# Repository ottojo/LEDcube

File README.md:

# LEDcube

Small LED Cube using SK6812 LEDs in 1515 package (1.5x1.5mm)

5 Sides with 4x4 LEDs each

Project on aisler.net: [https://aisler.net/p/QNEPCGOU](https://aisler.net/p/QNEPCGOU)

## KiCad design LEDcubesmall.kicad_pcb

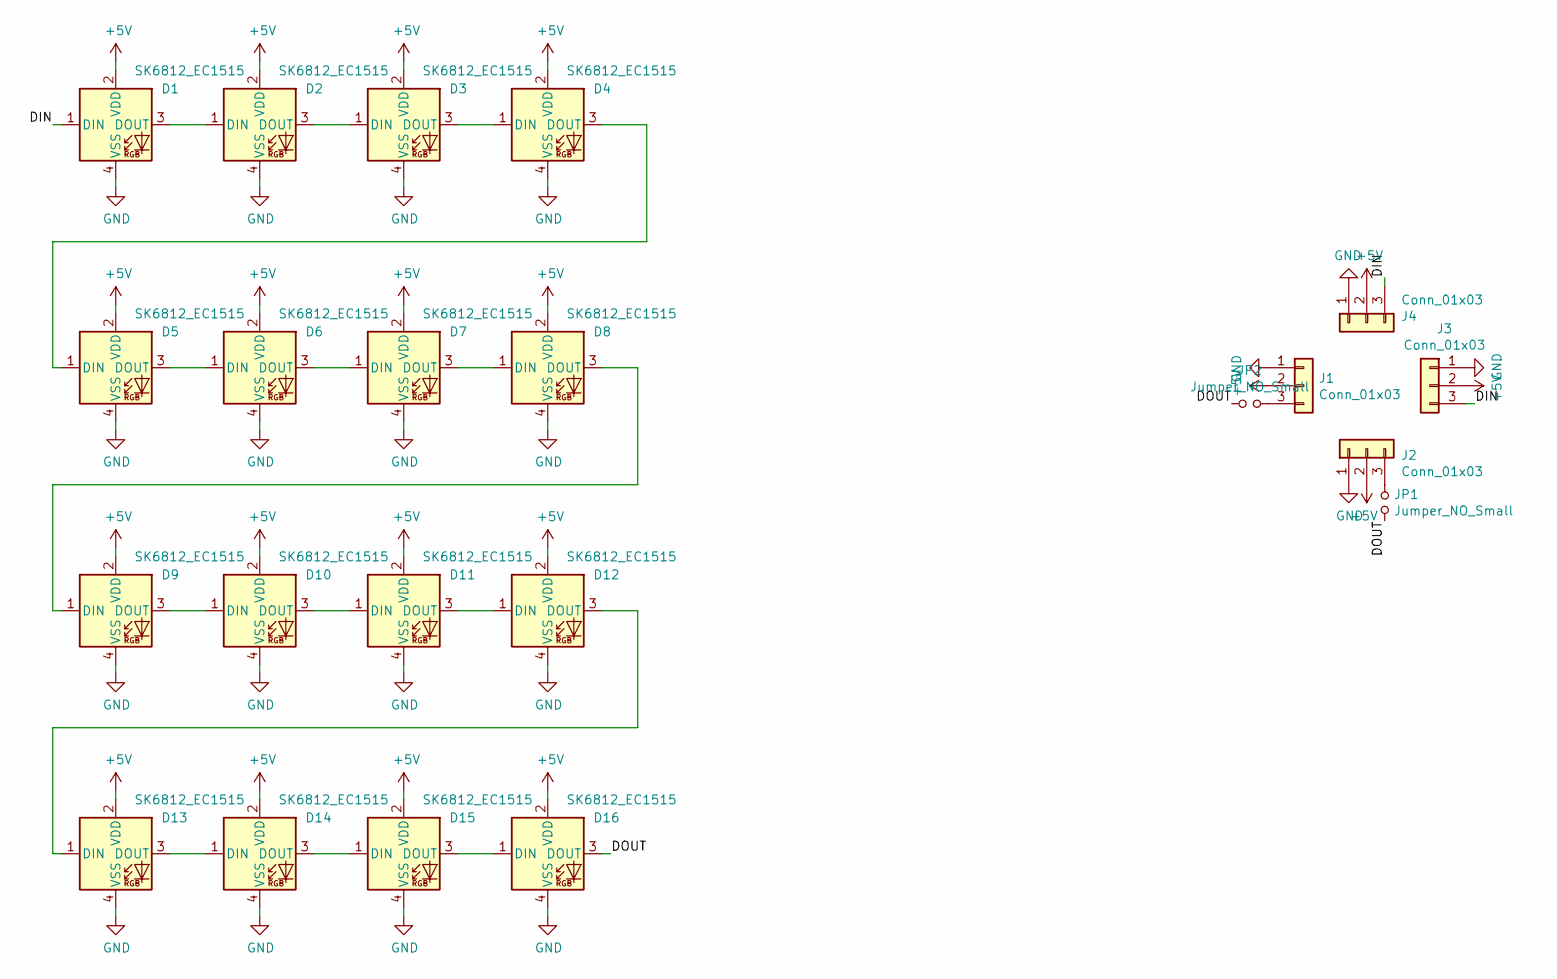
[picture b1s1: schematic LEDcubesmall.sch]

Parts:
D1, D2, D3, D4, D5, D6, D7, D8, D9, D10, D11, D12, D13, D14, D15, D16: SK6812_EC1515; LED_SK6812_EC1515
J1, J2, J3, J4: Conn_01x03; SolderJumper-3_P1.3mm_Open_Pad1.0x1.5mm
JP1, JP2: Jumper_NO_Small; SolderJumper-2_P1.3mm_Open_TrianglePad1.0x1.5mm

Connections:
+5V: D1.2 (VDD), D2.2 (VDD), D3.2 (VDD), D4.2 (VDD), D5.2 (VDD), D6.2 (VDD), D7.2 (VDD), D8.2 (VDD), D9.2 (VDD), D10.2 (VDD), D11.2 (VDD), D12.2 (VDD), D13.2 (VDD), D14.2 (VDD), D15.2 (VDD), D16.2 (VDD), J1.2, J2.2, J3.2, J4.2
/DIN: D1.1 (DIN), J3.3, J4.3
/DOUT: D16.3 (DOUT), JP1.1, JP2.1
GND: D1.4 (VSS), D2.4 (VSS), D3.4 (VSS), D4.4 (VSS), D5.4 (VSS), D6.4 (VSS), D7.4 (VSS), D8.4 (VSS), D9.4 (VSS), D10.4 (VSS), D11.4 (VSS), D12.4 (VSS), D13.4 (VSS), D14.4 (VSS), D15.4 (VSS), D16.4 (VSS), J1.1, J2.1, J3.1, J4.1
unnamed: D1.3 (DOUT), D2.1 (DIN)
unnamed: D2.3 (DOUT), D3.1 (DIN)
unnamed: D3.3 (DOUT), D4.1 (DIN)
unnamed: D4.3 (DOUT), D5.1 (DIN)
unnamed: D5.3 (DOUT), D6.1 (DIN)
unnamed: D6.3 (DOUT), D7.1 (DIN)
unnamed: D7.3 (DOUT), D8.1 (DIN)
unnamed: D8.3 (DOUT), D9.1 (DIN)
unnamed: D9.3 (DOUT), D10.1 (DIN)
unnamed: D10.3 (DOUT), D11.1 (DIN)
unnamed: D11.3 (DOUT), D12.1 (DIN)
unnamed: D12.3 (DOUT), D13.1 (DIN)
unnamed: D13.3 (DOUT), D14.1 (DIN)
unnamed: D14.3 (DOUT), D15.1 (DIN)
unnamed: D15.3 (DOUT), D16.1 (DIN)
unnamed: J1.3, JP2.2
unnamed: J2.3, JP1.2

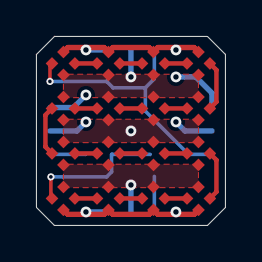
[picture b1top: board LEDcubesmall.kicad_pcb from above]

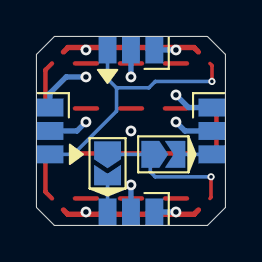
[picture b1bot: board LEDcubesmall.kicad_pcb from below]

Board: 4 copper layers, 10.5 x 10.5 mm, 22 parts (6 on the bottom side), 21 nets.

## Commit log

2019-09-25 adds license
2019-09-25 add gitignore
2019-09-25 corners, add missing gnd connection
